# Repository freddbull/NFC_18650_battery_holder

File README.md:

# NFC_18650_battery_holder
Battery holder for 18650 with NFC antenna and ST25DV ic

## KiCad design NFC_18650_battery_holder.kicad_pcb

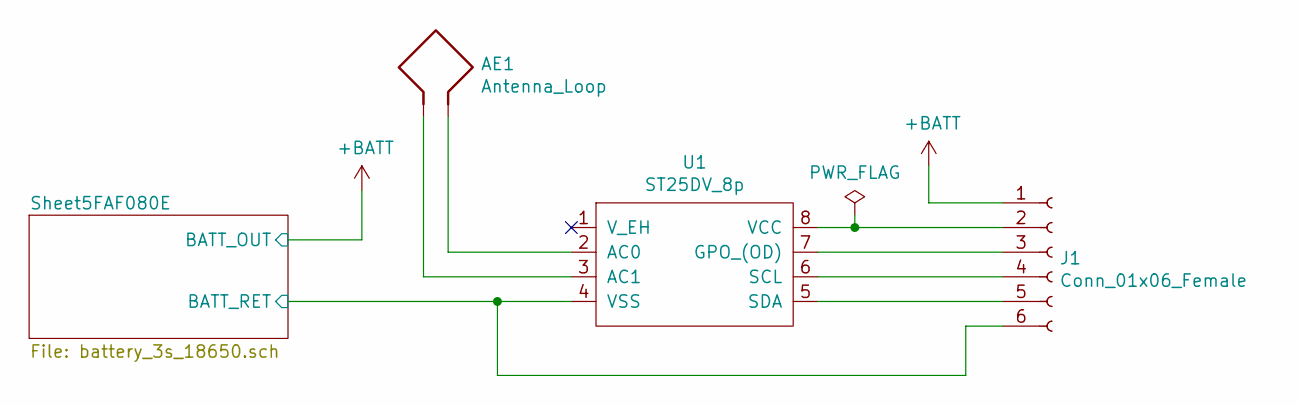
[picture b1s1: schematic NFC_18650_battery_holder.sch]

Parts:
AE1: Antenna_Loop; Antenna_4.32uH
J1: Conn_01x06_Female; JST_XH_B6B-XH-A_1x06_P2.50mm_Vertical
U1: ST25DV_8p; SOP-8_3.9x4.9mm_P1.27mm

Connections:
+BATT: J1.1; also elsewhere on the board
/Sheet5FAF080E/BATT_RET: J1.6, U1.4 (VSS); also elsewhere on the board
unnamed: AE1.1, U1.3 (AC1)
unnamed: AE1.2, U1.2 (AC0)
unnamed: J1.2, U1.8 (VCC)
unnamed: J1.3, U1.7 (GPO_(OD))
unnamed: J1.4, U1.6 (SCL)
unnamed: J1.5, U1.5 (SDA)

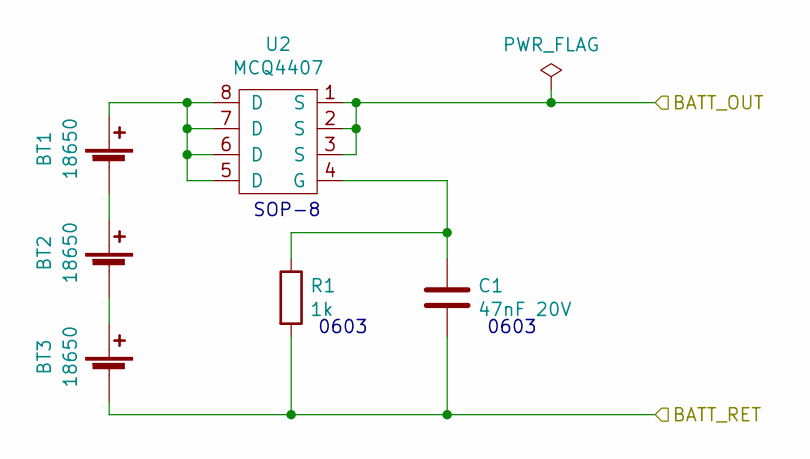
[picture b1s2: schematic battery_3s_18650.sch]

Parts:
BT1, BT2, BT3: 18650; 18650_holder_SMD_65mm
C1: 47nF 20V; C_0603_1608Metric_Pad1.05x0.95mm_HandSolder
R1: 1k; R_0603_1608Metric_Pad1.05x0.95mm_HandSolder
U2: MCQ4407; SOP-8_3.9x4.9mm_P1.27mm

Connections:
+BATT: U2.1 (S), U2.2 (S), U2.3 (S); also elsewhere on the board
/Sheet5FAF080E/BATT_RET: BT3.2 (-), C1.2, R1.2; also elsewhere on the board
unnamed: BT1.1 (+), U2.5 (D), U2.6 (D), U2.7 (D), U2.8 (D)
unnamed: BT1.2 (-), BT2.1 (+)
unnamed: BT2.2 (-), BT3.1 (+)
unnamed: C1.1, R1.1, U2.4 (G)

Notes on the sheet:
0603
SOP-8

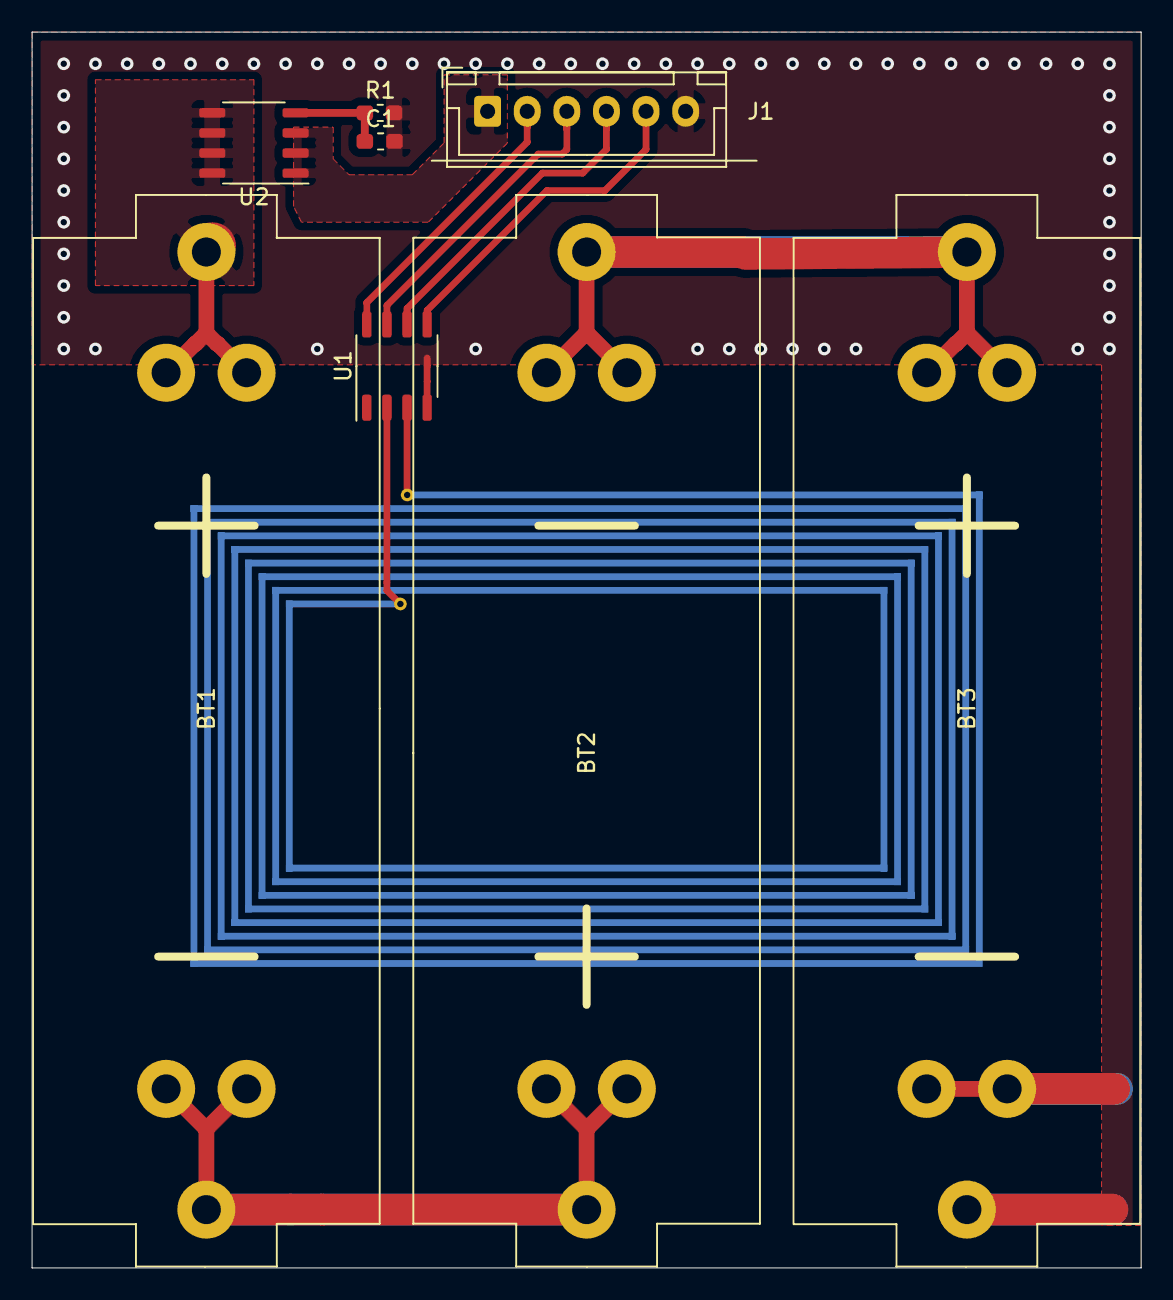
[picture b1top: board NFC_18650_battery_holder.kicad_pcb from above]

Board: 2 copper layers, 70.0 x 78.0 mm, 9 parts (1 on the bottom side), 12 nets.

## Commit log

2020-11-13 Initial commit for this KiCad project
2020-11-13 Project structure created. New symbol for ST25DV_8p created
2020-11-14 Schematic done.
2020-11-14 Added gitignore file to exclude large simulation files
2020-11-14 Library files added from NFC_hatch projekt. Started to work at the layout. 18650 holder footprint became wider 18 to 22mm.
2020-11-15 4.1uH antenna project done. Antenna was added to project via bitmap.
2020-11-15 Ignoring gerber files from github.
2020-11-15 Saved changes in datasheet.
2020-11-17 Antenna footprints done.
2020-11-17 4.32uH Antenna board done!
2020-11-17 4.10uH Antenna created. Couryard was added to battery footprint and vias were removed around battery as a result.
2020-11-18 Moved J1 1mm away from 18650 holder
